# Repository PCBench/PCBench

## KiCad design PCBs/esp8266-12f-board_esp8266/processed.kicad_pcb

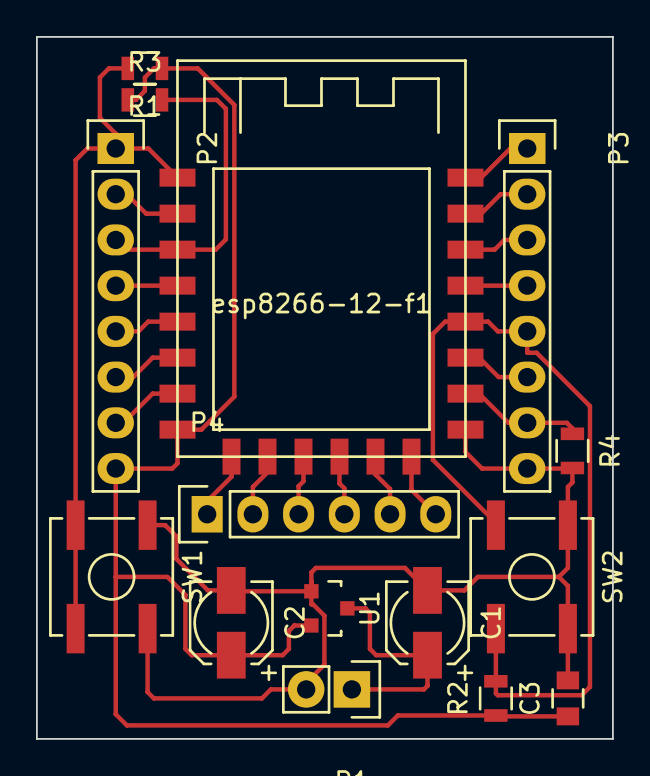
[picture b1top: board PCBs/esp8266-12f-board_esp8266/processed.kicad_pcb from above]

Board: 2 copper layers, 32.0 x 39.0 mm, 15 parts (0 on the bottom side), 23 nets.

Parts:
C1, C2: 10μf; c_elec_4x5.8
C3: 100μ; C_0805
P1: VIN; Socket_Strip_Straight_1x02
P2, P3: CONN_01X08; Socket_Strip_Straight_1x08
P4: CONN_01X06; Socket_Strip_Straight_1x06
R1, R2, R3, R4: 10K; R_0805
SW1, SW2: SW_PUSH; SW_SPST_B3SL-1002P
U1: APE8865N-33-HF-3; SOT-23
esp8266-12-f1: esp8266-12f

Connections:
/ADC: P2.2, esp8266-12-f1.2
/CS0: P4.1, esp8266-12-f1.9
/EN: P2.3, R3.2, esp8266-12-f1.3
/GPIO0: P3.5, R2.2, SW2.2, esp8266-12-f1.18
/GPIO2: P3.6, esp8266-12-f1.17
/GPIO4: P3.4, esp8266-12-f1.19
/GPIO5: P3.3, esp8266-12-f1.20
/GPIO9: P4.3, esp8266-12-f1.11
/GPIO10: P4.4, esp8266-12-f1.12
/GPIO12: P2.6, esp8266-12-f1.6
/GPIO13: P2.7, esp8266-12-f1.7
/GPIO14: P2.5, esp8266-12-f1.5
/GPIO15: P3.7, R4.1, esp8266-12-f1.16
/GPIO16: P2.4, esp8266-12-f1.4
/MISO: P4.2, esp8266-12-f1.10
/MOSI: P4.5, esp8266-12-f1.13
/RST: P2.1, R1.2, SW1.2, esp8266-12-f1.1
/RXD: P3.2, esp8266-12-f1.21
/SCLK: P4.6, esp8266-12-f1.14
/TXD: P3.1, esp8266-12-f1.22
GND: C1.2, C2.2, C3.2, P1.2, P3.8, R4.2, SW1.1, SW2.1, U1.1, esp8266-12-f1.15
unnamed: C1.1, P1.1, U1.3
VCC: C2.1, C3.1, P2.8, R1.1, R2.1, R3.1, U1.2, esp8266-12-f1.8

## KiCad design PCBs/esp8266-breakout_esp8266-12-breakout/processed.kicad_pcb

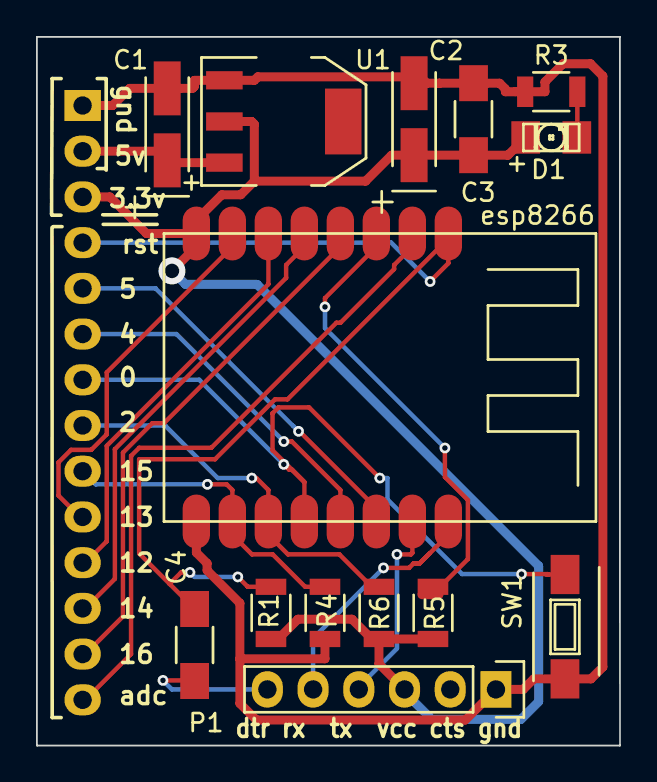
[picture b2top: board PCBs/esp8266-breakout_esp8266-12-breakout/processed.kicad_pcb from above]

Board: 2 copper layers, 32.4 x 39.4 mm, 15 parts (1 on the bottom side), 19 nets.

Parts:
C1, C2: 10uf; TantalC_SizeA_EIA-3216_HandSoldering
C3: 0.1uf; C_1206_HandSoldering
C4: 1uf; C_1206_HandSoldering
D1: LED; LED-1206
P1: ftdi; Pin_Header_Straight_1x06
P2: CONN_01X14; Pin_Header_Straight_1x14
R1, R4, R5, R6: 10k; R_1206
R3: 68r; R_1206
SW1: SW_PUSH; SW_SPST_FSMSM
U1: AP1117D33; SOT-223
esp8266: U2; esp8266-12

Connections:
+3V3: C2.1, C3.1, D1.2, P1.3, P2.3, R1.1, R4.1, R5.1, U1.2, esp8266.8
+5V: C1.1, P2.2, U1.3
/adc: P2.14, esp8266.2
/ch_pd: R5.2, esp8266.3
/gpio0: P2.7, SW1.1, esp8266.12
/gpio2: P2.8, R4.2, esp8266.11
/gpio4: P2.6, esp8266.13
/gpio5: P2.5, esp8266.14
/gpio12: P2.11, esp8266.6
/gpio13: P2.10, esp8266.7
/gpio14: P2.12, esp8266.5
/gpio15: P2.9, R6.1, esp8266.10
/gpio16: P2.13, esp8266.4
/reset: C4.2, P2.4, R1.2, esp8266.1
/rx: P1.4, esp8266.15
/tx: P1.5, esp8266.16
GND: C1.2, C2.2, C3.2, P1.1, P2.1, R3.2, R6.2, SW1.2, U1.1, esp8266.9
unnamed: C4.1, P1.6
unnamed: D1.1, R3.1

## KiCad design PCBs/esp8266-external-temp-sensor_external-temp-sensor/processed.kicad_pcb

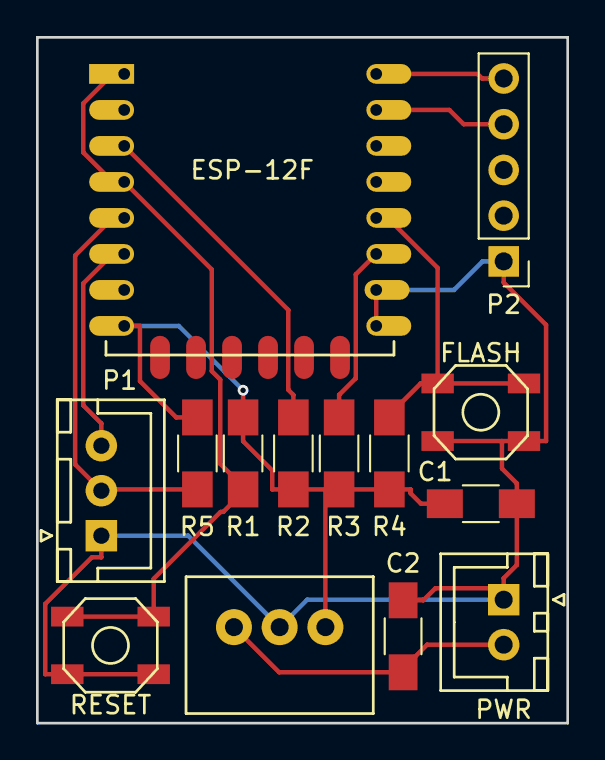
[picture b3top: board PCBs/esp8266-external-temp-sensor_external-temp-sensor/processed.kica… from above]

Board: 2 copper layers, 29.5 x 38.1 mm, 14 parts (0 on the bottom side), 11 nets.

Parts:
C1, C2: 10uF; C_1206_HandSoldering
P1: TEMP; JST_XH_B03B-XH-A_03x2.50mm_Straight
P2: SERIAL; Pin_Header_Straight_1x05_Pitch2.54mm
P3: PWR; JST_XH_B02B-XH-A_02x2.50mm_Straight
R1, R2, R3, R4, R5: 4.7K; R_1206_HandSoldering
SW1: RESET; SKQGAFE010_Switch
SW2: FLASH; SKQGAFE010_Switch
U1: ESP-12F; ESP-12E
U2: OKI-78SR

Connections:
/CH_EN: R2.2, U1.3
/DS18B20_DQ: P1.2, R5.2, U1.5
/DS18B20_PWR: P1.3, U1.6
/FLASH: R4.2, SW2.1, SW2.2, U1.18
/RESET: R1.2, SW1.1, SW1.2, U1.1, U1.4
/RX: P2.4, U1.21
/TX: P2.5, U1.22
GND: C1.2, C2.2, P1.1, P2.1, P3.1, SW1.3, SW1.4, SW2.3, SW2.4, U1.15, U1.16, U2.2
unnamed: C2.1, P3.2, U2.1
unnamed: R3.2, U1.17
VCC: C1.1, R1.1, R2.1, R3.1, R4.1, R5.1, U1.8, U2.3

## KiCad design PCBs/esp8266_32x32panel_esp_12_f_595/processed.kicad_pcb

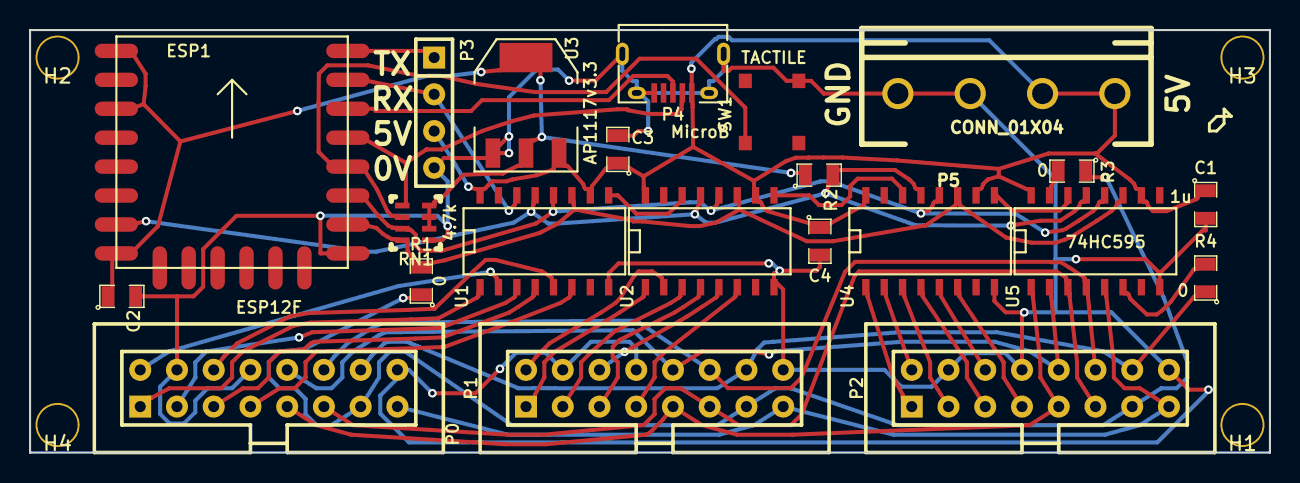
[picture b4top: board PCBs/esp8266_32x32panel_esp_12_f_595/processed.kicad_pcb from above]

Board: 2 copper layers, 85.7 x 29.2 mm, 26 parts (0 on the bottom side), 41 nets.

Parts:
C1, C2, C3, C4: 1u; SM0805
ESP1: ESP12F; ESP12E
H1, H2, H3, H4: MH; SMTPIN
P0, P1, P2: RGB_OUT; RECT_20x2
P3: CONN_01X04; RECT_4x1
P4: MicroB; USBMicroB-10118194-0001LF
P5: CONN_01X04; PHOENIX1933202
R1, R3, R4: 0; SM0805
R2: 10k; SM0805
RN1: 4.7k; NETWORK1206
SW1: TACTILE
U1, U2, U4, U5: 74HC595; SO-16-N
U3: AP1117v3.3; SOT-223

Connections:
+3V3: C2.1, ESP1.1, ESP1.3, ESP1.8, R2.1, RN1.6, RN1.7, RN1.8, U3.2, U3.4
+5V: C1.1, C3.1, C4.1, P3.3, P4.1, P5.1, P5.2, U1.10, U1.16, U2.10, U2.16, U3.3, U4.10, U4.16, U5.10, U5.16
A: P0.9, P1.9, P2.9, U5.1
B: P0.10, P1.10, P2.10, U5.2
B0_0: P0.3, U1.3
B0_1: P1.3, U2.3
B0_2: P2.3, U4.3
B1_0: P0.7, U1.6
B1_1: P1.7, U2.6
B1_2: P2.7, U4.6
BCK: ESP1.16, R1.2, RN1.4, U1.11, U2.11, U4.11, U5.11
C: P0.11, P1.11, P2.11, U5.3
CLK: P0.13, P1.13, P2.13, R1.1, R3.1
D: P0.12, P1.12, P2.12, U5.4
D+: ESP1.20, P4.3
D-: ESP1.19, P4.2, RN1.1
ECLK: R3.2, U5.15
ESTB: R4.2, U5.6
G0_0: P0.2, U1.2
G0_1: P1.2, U2.2
G0_2: P2.2, U4.2
G1_0: P0.6, U1.5
G1_1: P1.6, U2.5
G1_2: P2.6, U4.5
GND: C1.2, C2.2, C3.2, C4.2, ESP1.15, P0.4, P0.8, P0.16, P1.4, P1.8, P1.16, P2.4, P2.8, P2.16, P3.4, P4.5, P4.6, P4.7, P4.8, P4.9, P5.3, P5.4, RN1.5, SW1.4, U1.8, U2.8, U3.1, U4.8, U5.8
GPIO0: ESP1.18, RN1.2, SW1.1
OE: P0.15, P1.15, P2.15, U5.5
OEX: ESP1.7, R2.2, U1.13, U2.13, U4.13, U5.13
R0_0: P0.1, U1.1
R0_1: P1.1, U2.1
R0_2: P2.1, U4.1
R1_0: P0.5, U1.4
R1_1: P1.5, U2.4
R1_2: P2.5, U4.4
SDI: ESP1.21, P3.2, U1.14
SER1: U1.9, U2.14
SER2: U2.9, U4.14
SER3: U4.9, U5.14
STB: P0.14, P1.14, P2.14, R4.1
TX: ESP1.22, P3.1
WCK: ESP1.17, RN1.3, U1.12, U2.12, U4.12, U5.12

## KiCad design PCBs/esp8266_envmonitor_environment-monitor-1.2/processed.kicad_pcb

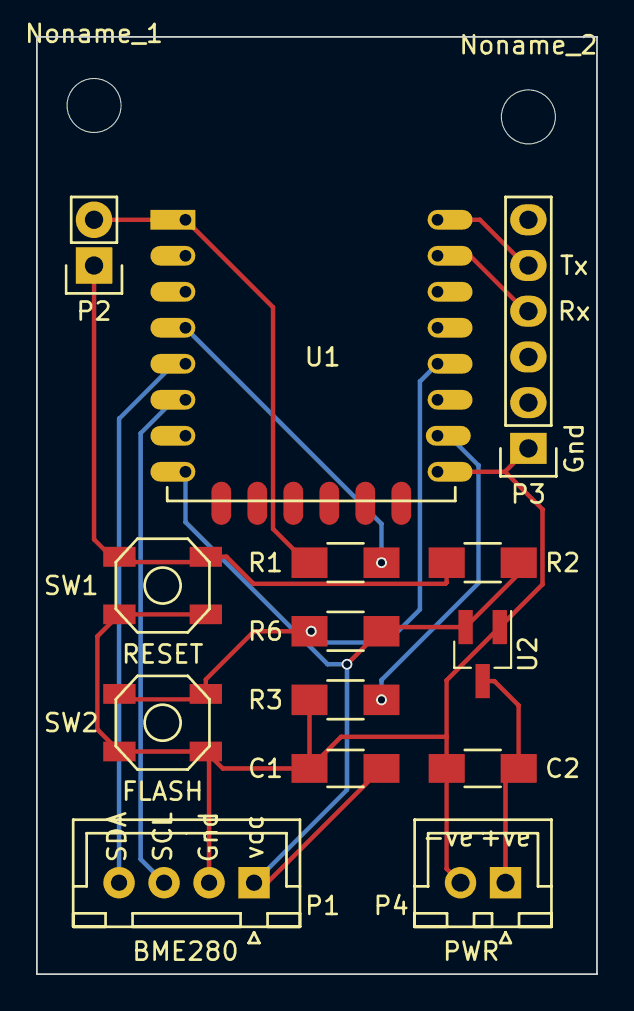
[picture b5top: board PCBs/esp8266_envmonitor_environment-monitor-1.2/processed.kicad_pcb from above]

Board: 2 copper layers, 31.1 x 52.1 mm, 16 parts (0 on the bottom side), 12 nets.

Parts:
C1: 1uF; C_1206_HandSoldering
C2: 10uF; C_1206_HandSoldering
Noname_1, Noname_2: MountingHole_3mm
P1: BME280; JST_XH_B04B-XH-A_04x2.50mm_Straight
P2: HEADER; Pin_Header_Straight_1x02
P3: SERIAL; Pin_Header_Straight_1x06
P4: PWR; JST_XH_B02B-XH-A_02x2.50mm_Straight
R1: 10R; R_1206_HandSoldering
R2, R3, R6: 10k; R_1206_HandSoldering
SW1: RESET; SKQGAFE010_Switch
SW2: FLASH; SKQGAFE010_Switch
U1: ESP-12E
U2: MCP1700T-3302E/TT; SOT-23_Handsoldering

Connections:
/FLASH: R6.2, SW2.1, SW2.2, U1.18
/RXD: P3.4, U1.21
/SCL: P1.3, U1.6
/SDA: P1.4, U1.5
/TXD: P3.5, U1.22
GND: C1.2, C2.2, P1.2, P3.1, P4.2, R3.2, SW1.1, SW1.2, SW2.3, SW2.4, U1.15, U2.1
unnamed: C2.1, P4.1, U2.3
unnamed: P2.1, R2.2, SW1.3, SW1.4
unnamed: P2.2, R1.1, U1.1
unnamed: R1.2, U1.4
unnamed: R3.1, U1.16
VCC: C1.1, P1.1, R2.1, R6.1, U1.8, U2.2

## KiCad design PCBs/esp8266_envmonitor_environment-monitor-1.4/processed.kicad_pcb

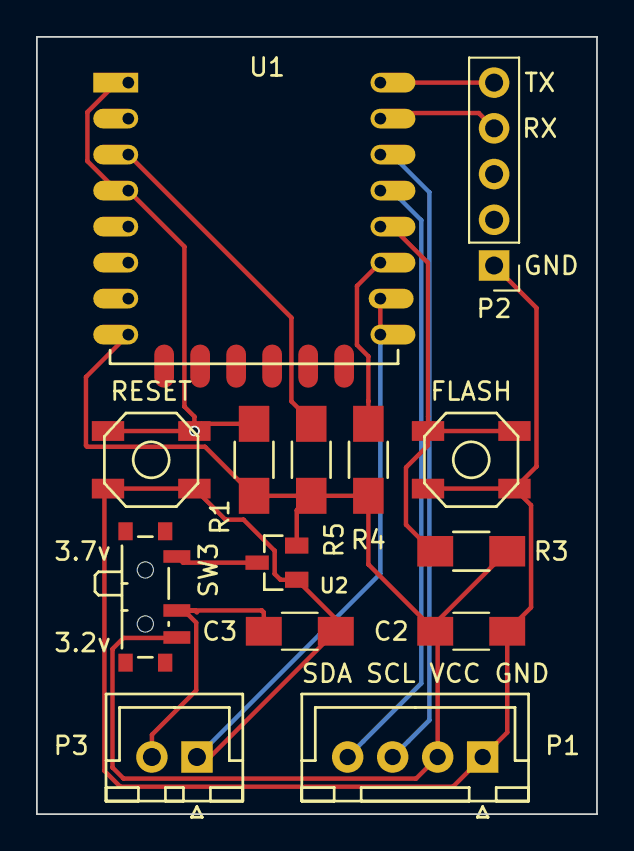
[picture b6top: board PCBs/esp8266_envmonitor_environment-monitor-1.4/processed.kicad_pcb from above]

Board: 2 copper layers, 31.1 x 43.2 mm, 14 parts (0 on the bottom side), 12 nets.

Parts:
C2: 10uF; C_1206_HandSoldering
C3: 1uF; C_1206_HandSoldering
P1: BME280; JST_XH_B04B-XH-A_04x2.50mm_Straight
P2: SERIAL; Pin_Header_Straight_1x05_Pitch2.54mm
P3: PWR; JST_XH_B02B-XH-A_02x2.50mm_Straight
R1, R3, R4, R5: 4.7k; R_1206_HandSoldering
SW1: RESET; SKQGAFE010_Switch
SW2: FLASH; SKQGAFE010_Switch
SW3: Switch_SPDT_x2; SW_SPDT_PCM12
U1: ESP-12F; ESP-12E
U2: MCP1700T; SOT-23

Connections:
/CH_EN: R5.2, U1.3
/FLASH: R3.2, SW2.1, SW2.2, U1.18
/RXD: P2.4, U1.21
/SCL: P1.3, U1.20
/SDA: P1.4, U1.19
/TXD: P2.5, U1.22
GND: C2.2, C3.2, P1.1, P2.1, P3.1, SW1.1, SW1.2, SW2.3, SW2.4, U1.15, U1.16, U2.1
unnamed: C3.1, P3.2, SW3.2
unnamed: R1.2, SW1.3, SW1.4, U1.1, U1.4
unnamed: R4.2, U1.17
unnamed: SW3.1, U2.3
VCC: C2.1, P1.2, R1.1, R3.1, R4.1, R5.1, SW3.3, U1.8, U2.2

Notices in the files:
PCBs/esp8266-external-temp-sensor_external-temp-sensor/processed.kicad_pcb:
Solderpad Hardware License version 0.51
PCBs/esp8266_envmonitor_environment-monitor-1.2/processed.kicad_pcb:
Released under Solderpad Hardware License version 0.51
